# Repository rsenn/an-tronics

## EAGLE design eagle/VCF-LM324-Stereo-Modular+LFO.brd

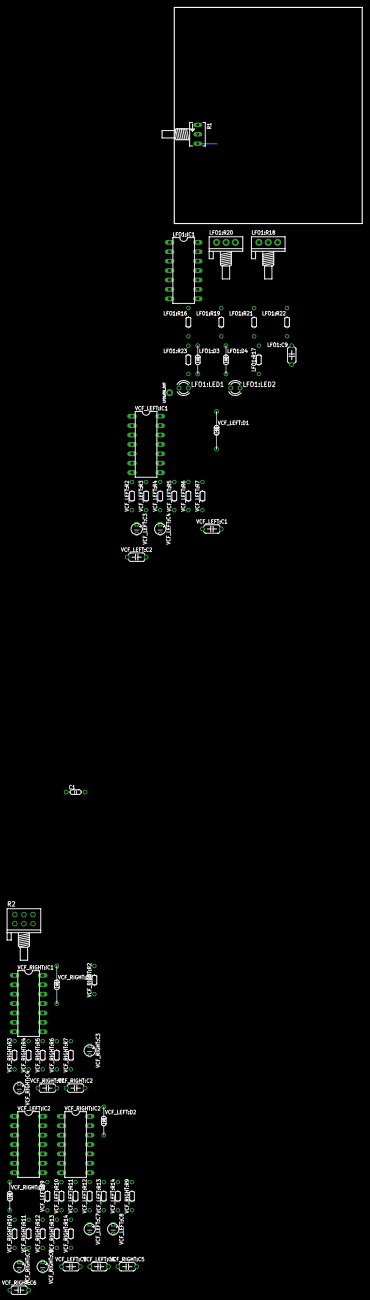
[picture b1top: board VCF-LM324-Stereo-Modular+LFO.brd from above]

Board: 2 copper layers, 50.8 x 58.4 mm, 66 parts (0 on the bottom side), 36 nets.

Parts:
C1: 100nF; C050-020X036
LFO1:C9: 1uF; C050-024X044/V
LFO1:D3, LFO1:D4: 1N4148; DO34-7V
LFO1:IC1: LM324; DIL14
LFO1:LED1, LFO1:LED2: LED3MM
LFO1:R16: 47k; 0202/7-V
LFO1:R17: 4.7k; 0202/7
LFO1:R18: 10k; POT
LFO1:R19: 4.7k; 0202/7-V
LFO1:R20: 100k; POT
LFO1:R21, LFO1:R22: 100k; 0202/7-V
LFO1:R23: 1k; 0202/7-V
LFO1:TRI_OUT: TRIANGLE; SPAD
R1: 100k; B64Y
R2: 10k; POT-STEREO
VCF_LEFT:C1, VCF_LEFT:C2, VCF_LEFT:C5, VCF_LEFT:C6: 100nF; C050-024X044
VCF_LEFT:C3, VCF_LEFT:C4, VCF_LEFT:C7, VCF_LEFT:C8: 1uF; E2,5-3
VCF_LEFT:D1: 1N4148; DO34-10V
VCF_LEFT:D2: 1N4148; DO34-7V
VCF_LEFT:IC1, VCF_LEFT:IC2: LM324; DIL14
VCF_LEFT:R2, VCF_LEFT:R3, VCF_LEFT:R9, VCF_LEFT:R10: 1k; 0202/7
VCF_LEFT:R4, VCF_LEFT:R11: 470k; 0202/7
VCF_LEFT:R5, VCF_LEFT:R6, VCF_LEFT:R7, VCF_LEFT:R12, VCF_LEFT:R13, VCF_LEFT:R14: 100k; 0202/7
VCF_RIGHT:C1, VCF_RIGHT:C2, VCF_RIGHT:C5, VCF_RIGHT:C6: 100nF; C050-024X044
VCF_RIGHT:C3, VCF_RIGHT:C4, VCF_RIGHT:C7, VCF_RIGHT:C8: 1uF; E2,5-3
VCF_RIGHT:D1: 1N4148; DO34-10V
VCF_RIGHT:D2: 1N4148; DO34-7V
VCF_RIGHT:IC1, VCF_RIGHT:IC2: LM324; DIL14
VCF_RIGHT:R2, VCF_RIGHT:R3, VCF_RIGHT:R9, VCF_RIGHT:R10: 1k; 0202/7
VCF_RIGHT:R4, VCF_RIGHT:R11: 470k; 0202/7
VCF_RIGHT:R5, VCF_RIGHT:R6, VCF_RIGHT:R7, VCF_RIGHT:R12, VCF_RIGHT:R13, VCF_RIGHT:R14: 100k; 0202/7

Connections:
CV_POT: R1.S, VCF_LEFT:R2.2, VCF_RIGHT:R2.2
GND: C1.2, LFO1:R22.1, R1.A, VCF_LEFT:D1.C, VCF_LEFT:D2.C, VCF_LEFT:IC1.11, VCF_LEFT:R6.1, VCF_LEFT:R13.1, VCF_RIGHT:D1.C, VCF_RIGHT:D2.C, VCF_RIGHT:IC1.11, VCF_RIGHT:R6.1, VCF_RIGHT:R13.1
LFO1:N$14: LFO1:IC1.7, LFO1:R16.2, LFO1:R19.1
LFO1:N$15: LFO1:IC1.5, LFO1:LED1.A, LFO1:LED2.K, LFO1:R16.1
LFO1:N$26: LFO1:C9.1, LFO1:D3.C, LFO1:D4.A, LFO1:IC1.9
LFO1:N$28: LFO1:C9.2, LFO1:IC1.8, LFO1:LED1.K, LFO1:LED2.A, LFO1:R23.2
LFO1:OA_C_IN+: LFO1:IC1.6, LFO1:IC1.10, LFO1:R21.1, LFO1:R22.2
LFO1:TRIM_1_A: LFO1:D3.A, LFO1:R20.1
LFO1:TRIM_1_B: LFO1:D4.C, LFO1:R20.3
LFO1:TRIM_2_A: LFO1:R17.1, LFO1:R18.3
LFO1:TRIM_2_B: LFO1:R18.1, LFO1:R19.2
LFO1:TRIM_P: LFO1:R17.2, LFO1:R18.2, LFO1:R20.2
unnamed: R2.1-2, R2.1-3, VCF_LEFT:C3.+, VCF_LEFT:IC1.1, VCF_LEFT:R7.2
unnamed: R2.1-1, VCF_LEFT:C2.2
unnamed: R2.2-2, R2.2-3, VCF_RIGHT:C3.+, VCF_RIGHT:IC1.1, VCF_RIGHT:R7.2
unnamed: R2.2-1, VCF_RIGHT:C2.2
unnamed: LFO1:R23.1, LFO1:TRI_OUT.1, VCF_LEFT:R3.2, VCF_RIGHT:R3.2
VCC: C1.1, LFO1:R21.2, R1.E, VCF_LEFT:IC1.4, VCF_LEFT:R5.1, VCF_LEFT:R12.1, VCF_RIGHT:IC1.4, VCF_RIGHT:R5.1, VCF_RIGHT:R12.1
VCF_LEFT:N$2: VCF_LEFT:C1.1, VCF_LEFT:IC1.2, VCF_LEFT:R4.2, VCF_LEFT:R7.1
VCF_LEFT:N$7: VCF_LEFT:IC1.3, VCF_LEFT:R5.2, VCF_LEFT:R6.2
VCF_LEFT:N$9: VCF_LEFT:C1.2, VCF_LEFT:C2.1, VCF_LEFT:D1.A, VCF_LEFT:R2.1, VCF_LEFT:R3.1
VCF_LEFT:N$10: VCF_LEFT:C4.-, VCF_LEFT:R4.1
VCF_LEFT:N$13: VCF_LEFT:IC2.13, VCF_LEFT:R12.2, VCF_LEFT:R13.2
VCF_LEFT:N$16: VCF_LEFT:C5.2, VCF_LEFT:C6.1, VCF_LEFT:D2.A, VCF_LEFT:R9.1, VCF_LEFT:R10.1
VCF_LEFT:N$17: VCF_LEFT:C5.1, VCF_LEFT:IC2.12, VCF_LEFT:R11.2, VCF_LEFT:R14.1
VCF_LEFT:N$20: VCF_LEFT:C8.-, VCF_LEFT:R11.1
VCF_LEFT:R_P_R_IN: VCF_LEFT:C7.+, VCF_LEFT:IC2.14, VCF_LEFT:R14.2
VCF_RIGHT:N$2: VCF_RIGHT:C1.1, VCF_RIGHT:IC1.2, VCF_RIGHT:R4.2, VCF_RIGHT:R7.1
VCF_RIGHT:N$7: VCF_RIGHT:IC1.3, VCF_RIGHT:R5.2, VCF_RIGHT:R6.2
VCF_RIGHT:N$9: VCF_RIGHT:C1.2, VCF_RIGHT:C2.1, VCF_RIGHT:D1.A, VCF_RIGHT:R2.1, VCF_RIGHT:R3.1
VCF_RIGHT:N$10: VCF_RIGHT:C4.-, VCF_RIGHT:R4.1
VCF_RIGHT:N$13: VCF_RIGHT:IC2.13, VCF_RIGHT:R12.2, VCF_RIGHT:R13.2
VCF_RIGHT:N$16: VCF_RIGHT:C5.2, VCF_RIGHT:C6.1, VCF_RIGHT:D2.A, VCF_RIGHT:R9.1, VCF_RIGHT:R10.1
VCF_RIGHT:N$17: VCF_RIGHT:C5.1, VCF_RIGHT:IC2.12, VCF_RIGHT:R11.2, VCF_RIGHT:R14.1
VCF_RIGHT:N$20: VCF_RIGHT:C8.-, VCF_RIGHT:R11.1
VCF_RIGHT:R_P_R_IN: VCF_RIGHT:C7.+, VCF_RIGHT:IC2.14, VCF_RIGHT:R14.2

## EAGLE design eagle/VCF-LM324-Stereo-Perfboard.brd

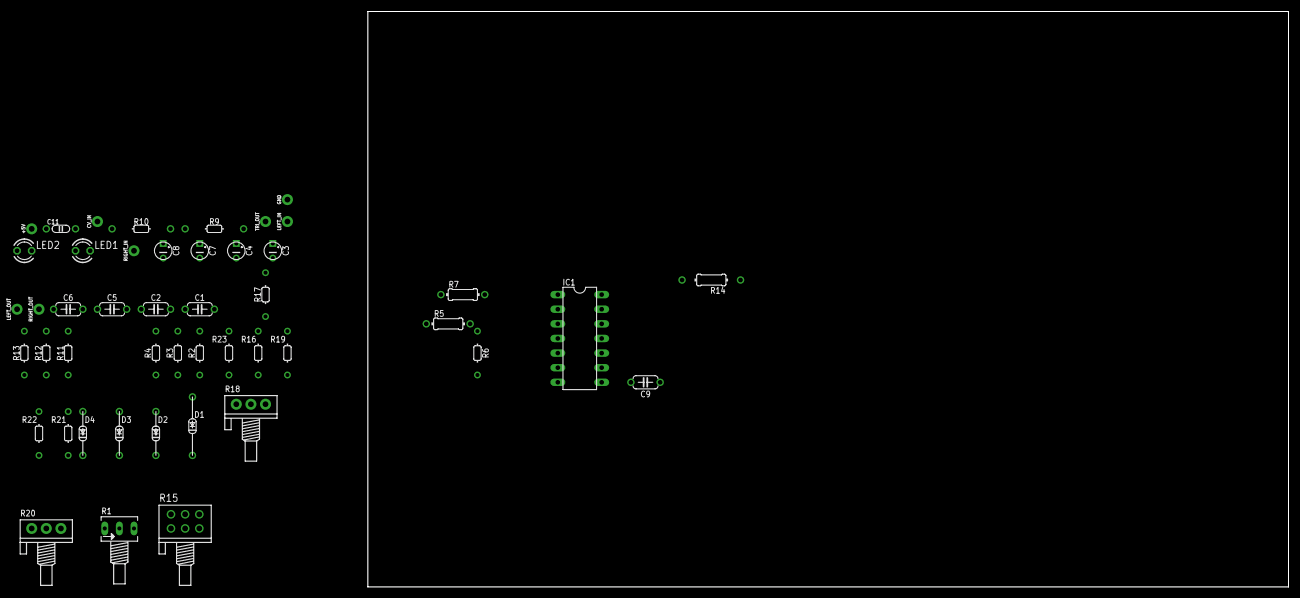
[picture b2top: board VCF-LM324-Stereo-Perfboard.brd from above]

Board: 2 copper layers, 160.0 x 100.0 mm, 47 parts (0 on the bottom side), 31 nets, no tracks yet.

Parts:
+5V: VCC; SPAD
C1, C2, C5, C6: 100nF; C050-024X044
C3, C4, C7, C8: 1μF; E2,5-3
C9: 1μF; C050-024X044
C11: 100nF; C050-020X036
CV_IN: CV_IN; SPAD
D1: 1N4148; DO34-10V
D2, D3, D4: 1N4148; DO34-7V
GND: GND; SPAD
IC1: LM324; DIL14
LED1, LED2: LED3MM
LEFT_IN: AUDIO_IN; SPAD
LEFT_OUT: AUDIO_OUT; SPAD
R1: 100kΩ; B64Y
R2, R3: 1kΩ; 0202/7
R4, R11: 470kΩ; 0202/7
R5, R7: 100kΩ; 0204/7
R6, R12, R13: 100kΩ; 0202/7
R9, R10: 1kΩ; 0202/10
R14: 100kΩ; 0204/10
R15: 10kΩ; POT-STEREO-2X3
R16: 47kΩ; 0202/7-V
R17: 4.7kΩ; 0202/7
R18: 10kΩ; POT
R19: 4.7kΩ; 0202/7-V
R20: 100kΩ; POT
R21, R22: 100kΩ; 0202/7-V
R23: 1kΩ; 0202/7-V
RIGHT_IN: AUDIO_IN; SPAD
RIGHT_OUT: AUDIO_OUT; SPAD
TRI_OUT: TRIANGLE; SPAD

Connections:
GND: C11.2, D1.C, D2.C, GND.1, IC1.11, R1.A, R6.1, R13.1, R22.1
unnamed: C4.+, LEFT_IN.1
unnamed: C1.1, IC1.2, R4.2, R7.1
unnamed: C2.2, R15.1-E
unnamed: C3.+, IC1.1, R7.2, R15.1-S
unnamed: C3.-, LEFT_OUT.1
unnamed: IC1.3, R5.2, R6.2
unnamed: CV_IN.1, R3.2, R10.2
unnamed: C1.2, C2.1, D1.A, R2.1, R3.1
unnamed: C4.-, R4.1
unnamed: C6.2, R15.2-E
unnamed: C7.+, IC1.14, R14.2, R15.2-S
unnamed: IC1.13, R12.2, R13.2
unnamed: IC1.7, R16.2, R19.1
unnamed: IC1.5, LED1.A, LED2.K, R16.1
unnamed: C5.2, C6.1, D2.A, R9.1, R10.1
unnamed: C5.1, IC1.12, R11.2, R14.1
unnamed: C7.-, RIGHT_OUT.1
unnamed: C8.+, RIGHT_IN.1
unnamed: C8.-, R11.1
unnamed: C9.1, D3.C, D4.A, IC1.9
unnamed: C9.2, IC1.8, LED1.K, LED2.A, R23.2
OA_C_IN+: IC1.6, IC1.10, R21.1, R22.2
TRIM_1_A: D3.A, R20.1
TRIM_1_B: D4.C, R20.3
TRIM_2_A: R17.1, R18.3
TRIM_2_B: R18.1, R19.2
TRIM_P: R17.2, R18.2, R20.2
TRI_OUT: R23.1, TRI_OUT.1
TUNE: R1.S, R2.2, R9.2
VCC: +5V.1, C11.1, IC1.4, R1.E, R5.1, R12.1, R21.2

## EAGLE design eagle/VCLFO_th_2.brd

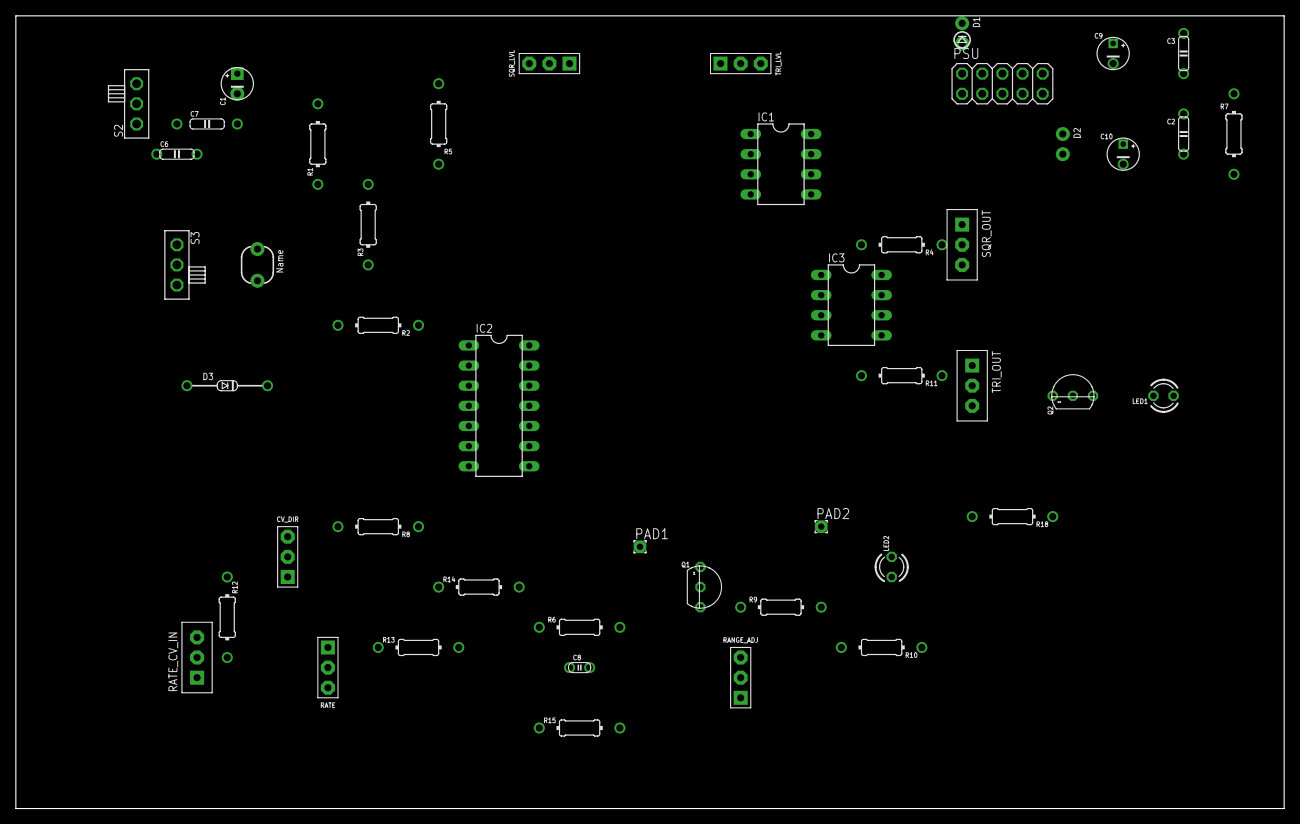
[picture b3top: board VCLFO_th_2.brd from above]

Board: 2 copper layers, 160.0 x 100.0 mm, 48 parts (0 on the bottom side), 35 nets, no tracks yet.

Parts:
C1: 10u bipolar; E2,5-4
C2, C3: 100n; C050-020X044/V
C6: 220nF; C050-020X044
C7: 4,7nF; C075-020X044
C8: 100p; C025-015X024
C9, C10: 10u; E2.5-4/V
CV_DIR: 10kΩ; CONN-3P
D1: Diode 1A 50V; DO35-2_54
D2: Diode 1A 50V; DO35-2_54A
D3: 1N4148; DO34-10
IC1, IC3: LM358N; DIL08
IC2: LM324N; DIL14
LED1, LED2: LED-3MM; LED_3MM
PAD1, PAD2: 1,6/0,8
PSU: 2X05
Q1, Q2: 2N3904; TO92
R1: 33kΩ; 0204/10
R2, R4, R11: 1kΩ; 0204/10
R3, R8, R12, R14, R15, R18: 100kΩ; 0204/10
R5: 220kΩ; 0204/10-V
R6: 4.7kΩ; 0204/10
R7: 27kΩ; 0204/10-V
R9, R10: 10kΩ; 0204/10
R13: 330kΩ; 0204/10
R17: Token PGM5539; PHOTOCELL
RANGE_ADJ: 10kΩ; CONN-3P
RATE: 10kΩ; CONN-3P
RATE_CV_IN: CONN-3P
S2: SKS07SP; SLSW-1P2T-H
S3: SKS04SP; SLSW-1P2T-H
SQR_LVL: 100kΩ; CONN-3P
SQR_OUT: CONN-3P
TRI_LVL: 100kΩ; CONN-3P
TRI_OUT: CONN-3P

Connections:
+12V: C3.1, C9.+, D1.C, IC1.8, IC2.4, IC3.8, R7.1
-12V: C2.2, C10.-, D2.A, IC1.4, IC2.11, IC3.4, RANGE_ADJ.3, RATE.3
GND: C2.1, C3.2, C9.-, C10.+, IC1.2, IC1.5, IC2.3, IC2.5, IC2.12, PSU.3, PSU.4, PSU.5, PSU.6, PSU.7, PSU.8, Q2.1, R10.1, RATE.1, RATE_CV_IN.1, RATE_CV_IN.3, SQR_LVL.1, SQR_OUT.1, TRI_LVL.1, TRI_OUT.1
unnamed: C7.1, IC1.6, R17.1, S2.2, S3.2
unnamed: D3.C, R2.2, R17.2
unnamed: IC3.1, IC3.2, R4.2
unnamed: R5.2, SQR_LVL.3
unnamed: IC1.3, R1.1, R3.2
unnamed: R4.1, SQR_OUT.2
unnamed: CV_DIR.3, IC2.2, R8.2
unnamed: IC3.6, IC3.7, R11.2
unnamed: IC3.3, SQR_LVL.2
unnamed: D1.A, PSU.1, PSU.2
unnamed: D2.C, PSU.9, PSU.10
unnamed: R12.2, RATE_CV_IN.2
unnamed: C8.2, IC2.14, PAD1.1, Q1.2, Q1.3, R6.2
unnamed: C1.+, S2.1
unnamed: CV_DIR.2, R12.1
unnamed: D3.A, S3.1
unnamed: R11.1, TRI_OUT.2
unnamed: R13.1, RATE.2
unnamed: C6.1, S2.3
unnamed: Q2.2, R18.1
unnamed: IC2.6, Q1.1, R9.1
unnamed: IC2.1, R8.1, R14.1
unnamed: C8.1, CV_DIR.1, IC2.13, R6.1, R13.2, R14.2, R15.1
unnamed: IC2.7, IC2.10, PAD2.1, R9.2
unnamed: R15.2, RANGE_ADJ.2
unnamed: IC2.8, LED2.K
unnamed: IC2.9, LED2.A, R10.2
unnamed: IC3.5, TRI_LVL.2
unnamed: LED1.K, Q2.3
unnamed: LED1.A, R7.2
SQR: IC1.1, R2.1, R3.1, R5.1
TRI: C1.-, C6.2, C7.2, IC1.7, R1.2, R18.2, TRI_LVL.3

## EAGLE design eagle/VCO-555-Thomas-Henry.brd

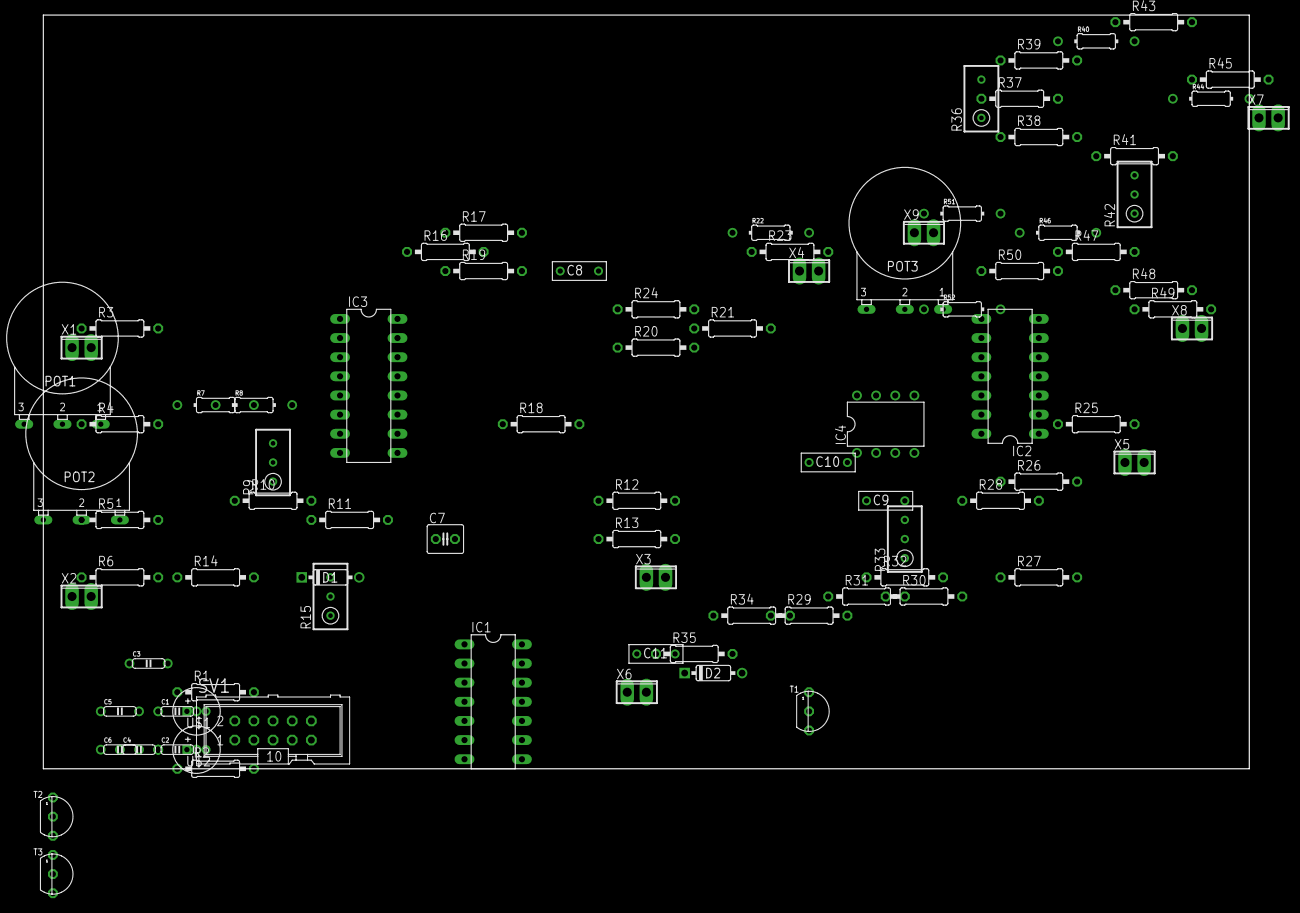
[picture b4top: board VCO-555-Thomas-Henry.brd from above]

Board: 2 copper layers, 160.0 x 100.0 mm, 87 parts (0 on the bottom side), 56 nets, no tracks yet.

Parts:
C1, C2, C3, C4, C5, C6: 100n; C050-020X044
C7: 100pF; C025-040X050
C8: 2.2nF; 072X025
C9: 100nF; 072X025
C10: 1nF; 072X025
C11: 470pF; 072X025
D1, D2: 1N4148-3; DO35-3
IC1, IC2: TL074P; DIL14
IC3: LM13700N; DIL16
IC4: NE555N; DIL08
POT1, POT2, POT3: 100k; 16MM
R1, R2: 11r; 0207/10
R3, R4, R6, R29, R30, R35, R39: 100k; 0207/10
R5: 3.3M; 0207/10
R7, R8: 1k; 0204/10
R9: 100r; RTRIM3296W
R10, R38: 390r; 0207/10
R11: 22k; 0207/10
R12: 1.5M; 0207/10
R13, R14, R32, R37: 1M; 0207/10
R15, R33, R36: 100k; RTRIM3296W
R16, R19: 1.5k; 0207/10
R17, R24, R26, R27, R28: 10k; 0207/10
R18, R34: 4.7k; 0207/10
R20, R21: 20k; 0207/10
R22: 2k; 0204/10
R23: 2k; 0207/10
R25, R45: 1k; 0207/10
R31: 150k; 0207/10
R40: 39k; 0204/10
R41: 39k; 0207/10
R42: 25k; RTRIM3296W
R43: 300k; 0207/10
R44: 5.6k; 0204/10
R46: 2.2k; 0204/10
R47: 2.2M; 0207/10
R48: 3k; 0207/10
R49: 1.8k; 0207/10
R50: 120k; 0207/10
R51: 100k; 0204/10
R52: 330k; 0204/10
SV1: ML10
T1, T2, T3: 2N3904; TO92
U$1, U$2: 47uF; 063_025
X1, X2, X3, X4, X5, X6, X7, X8, X9: 2POL254

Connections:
+15V: C1.1, C3.1, C5.1, C9.2, IC1.4, IC2.4, IC3.11, IC4.8, POT1.3, POT2.3, POT3.3, R1.1, R17.2, R24.1, R33.1, R34.1, R36.3, R42.1, R43.2, U$1.+
-15V: C2.2, C4.2, C6.2, IC1.11, IC2.11, IC3.6, POT1.1, POT2.1, POT3.1, R2.1, R12.2, R31.2, R33.3, R36.1, R44.1, U$2.-
GND: C1.2, C2.1, C3.2, C4.1, C5.2, C6.1, C8.2, C9.1, C10.2, D2.A, IC1.3, IC1.5, IC2.5, IC2.10, IC3.14, IC4.1, R10.2, R15.1, R16.2, R19.1, R20.2, R23.1, R38.2, R49.2, SV1.3, SV1.4, SV1.5, SV1.6, SV1.7, SV1.8, T1.1, T3.2, U$1.-, U$2.+, X1.2, X2.2, X3.2, X4.2, X5.2, X6.2, X7.2, X8.2, X9.2
unnamed: D1.C, R15.3
unnamed: R14.1, R15.2
unnamed: IC3.1, T2.3
unnamed: R2.2, SV1.2
unnamed: R1.2, SV1.10
unnamed: IC3.3, R18.1, R19.2
unnamed: IC3.4, R16.1, R17.1
unnamed: C8.1, IC1.10, IC3.5
unnamed: R3.2, X1.1
unnamed: POT1.2, R4.2
unnamed: POT2.2, R5.2
unnamed: R6.2, X2.1
unnamed: IC1.2, R3.1, R4.1, R5.1, R6.1, R7.1, R14.2
unnamed: R7.2, R8.1
unnamed: IC1.1, R8.2, R9.3
unnamed: R9.1, R10.1
unnamed: R9.2, T2.2
unnamed: R11.1, T2.1, T3.1
unnamed: C7.2, IC1.6
unnamed: R13.1, X3.1
unnamed: C7.1, D1.A, IC1.7, R11.2
unnamed: IC1.8, IC1.9, IC1.12, IC4.2, IC4.6, R29.2
unnamed: IC1.13, R20.1, R21.1, R24.2
unnamed: IC1.14, R21.2, R22.1, R39.1, R40.1, R46.2
unnamed: R22.2, R23.2, X4.1
unnamed: IC4.3, R18.2
unnamed: IC2.3, IC4.7, R28.2
unnamed: IC2.1, R25.1, R26.2
unnamed: IC2.2, R26.1, R27.2
unnamed: R25.2, X5.1
unnamed: IC2.6, R29.1, R30.2, R31.1, R32.2
unnamed: R36.2, R37.2
unnamed: IC2.7, R27.1, R28.1, R30.1
unnamed: R32.1, R33.2
unnamed: C10.1, IC4.5
unnamed: IC4.4, R34.2, T1.3
unnamed: D2.C, R35.2, T1.2
unnamed: C11.2, R35.1
unnamed: C11.1, X6.1
unnamed: IC3.16, R41.2
unnamed: R41.1, R42.2, R42.3
unnamed: IC2.12, R46.1, R47.2
unnamed: IC3.13, R37.1, R38.1, R39.2
unnamed: IC2.14, R47.1, R48.2
unnamed: R48.1, R49.1, X8.1
unnamed: IC3.10, IC3.12, R40.2, R43.1
unnamed: IC3.9, R44.2, R45.2
unnamed: R45.1, X7.1
unnamed: IC2.8, IC2.13, R50.1
unnamed: IC2.9, R50.2, R51.1, R52.1
unnamed: R51.2, X9.1
unnamed: POT3.2, R52.2
unnamed: R12.1, R13.2, T3.3

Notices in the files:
parts and their libraries:
SparkFun-Sensors: Licensing: Creative Commons ShareAlike 4.0 International - https://creativecommons.org/licenses/by-sa/4.0
